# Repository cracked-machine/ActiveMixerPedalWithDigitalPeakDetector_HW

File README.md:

## Active 4-way mixer pedal with digital peak detector

- Analog 4->1 mixer circuit with buffered inputs and input gain control.
- Digital LED peak detector per input channel.
- Fits in a Hammond 1590BB enclosure (120mm x 95mm).

Required Kicad Hardware library: https://github.com/cracked-machine/KicadLibrary

Related SW project: https://github.com/cracked-machine/DigitalPeakDetector_SW

### System Overview

### Schematic

##### Top Level

##### Input Buffer and Gain Block

This uses a split supply op amp. The second stage is an inverting op amp configuration so that it can attenuate the input signal down to zero output.
Therefore the second op amp has very low input impedance and will cause "tone-suck" if used on its own. The solution is to add a preceding op amp stage in a non-inverting configuration that works as a high input impedance buffer.

##### Negative Rail Block

Each ``Input Buffer and Gain Block`` requires a split power supply. We use a charge pump to provide a negative voltage rail. The small SOT23-5 package provides ~10mA current, which is enough for a dual opamp in this design.

##### MCU Peak Detector block

This section replaces the classic analog peak detector circuit with a microcontroller. The input signal is captured by the 12bit ADC of the microcontroller. The average input value and the output threshold are determined by software. When the output threshold is reached, the microcontroller briefly toggles the LED. The on/off time duration of the LED is also determined in software.

##### MCU Input Buffer block

This serves several purposes.
1. It acts as a high impedance buffer and low pass filter for the ADC. This helps to provide a cleaner input signal for the ADC by removing high frequency noise.
2. The 3.3V *single* supply of the op amp removes any parts of the input signal that swing above 3.3v and below ground (the limits of the microcontroller). In the event that a line level input signal was plugged into the input, the op amp would be damaged before the microcontroller.

##### Power Supply block

This linear regulator drops the 9VDC input to 3.3VDC. The power requirements of the system components are very low (~65mA) so the expected dissipation is also low (0.37W). A copper pad on both sides of the PCB (with connected vias) is provided to reduce this dissipation.

## 3D Renderings

__PCB__

__Front Panel__

__Back Panel__

__PCB and panel profile__

## TODO

Some issues with the HW design:

- The PSU uses 3.3V for both MCU and Analog blocks. This is too low for the opamps in the analog blocks and does not allow enough headroom for the signal. This can result in clipping of the signal.

- The charge pumps used by the opamps in the analog blocks (used to create a negative voltage rail) need filtering. The negative voltage rail is noisy (observed on the scope) and a high pitched whine can be heard through the output when plugged into a large amplifier. A simple passive LPF would probably solve this. 

- The output is on the wrong side!

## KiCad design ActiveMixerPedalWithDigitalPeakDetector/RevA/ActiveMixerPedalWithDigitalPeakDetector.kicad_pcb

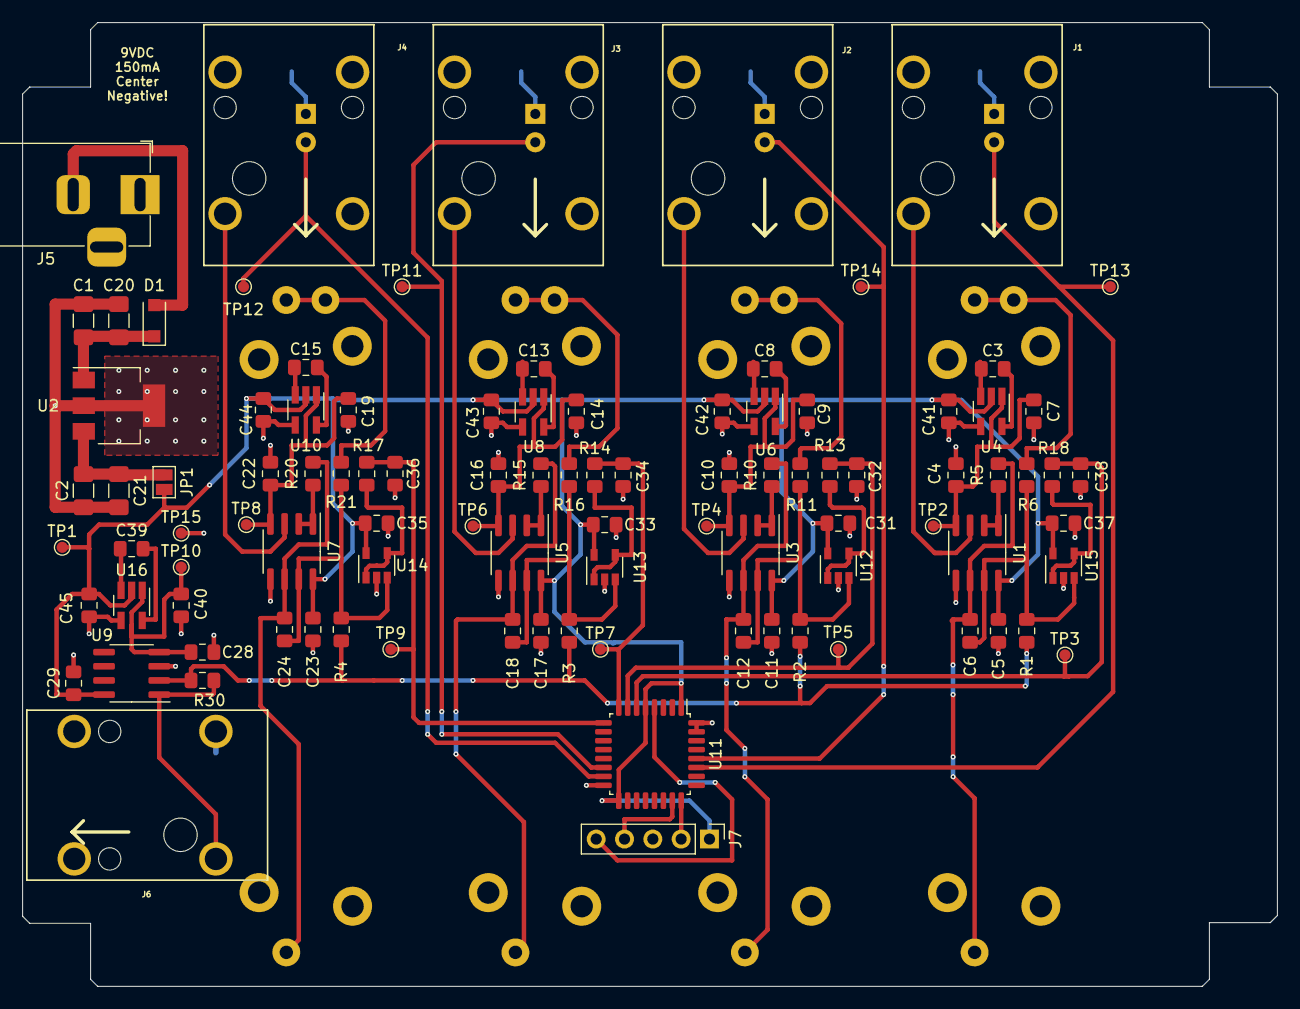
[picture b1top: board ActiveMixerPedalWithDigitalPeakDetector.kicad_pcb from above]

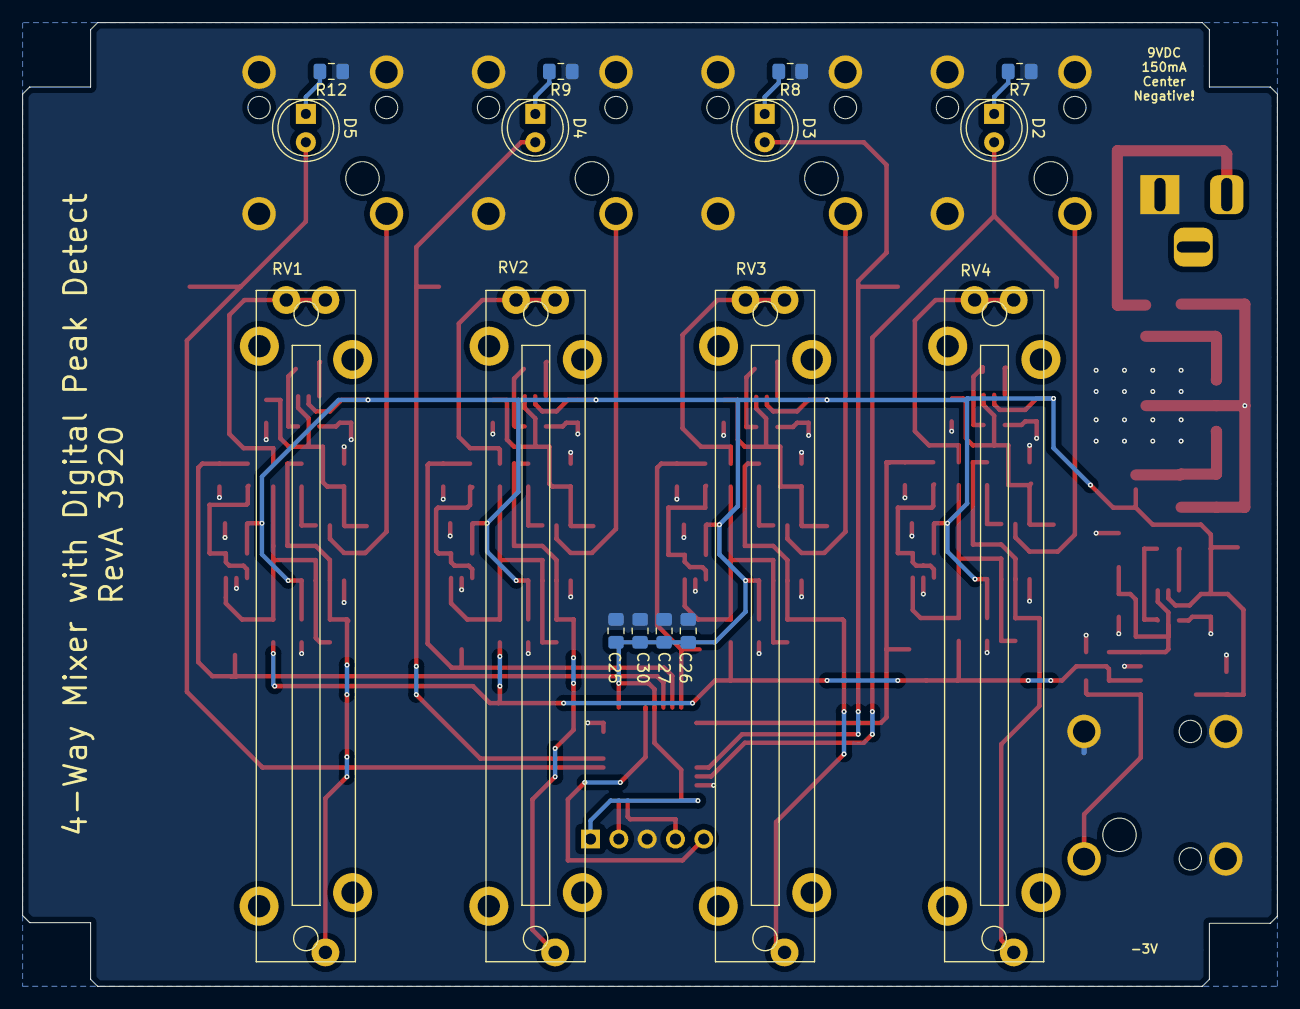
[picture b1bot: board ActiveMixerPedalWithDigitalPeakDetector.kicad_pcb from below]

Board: 2 copper layers, 112.5 x 86.4 mm, 114 parts (16 on the bottom side), 61 nets.

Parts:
C1, C21: 100nF; C_1206_3216Metric_Pad1.42x1.75mm_HandSolder
C2, C20: 1uF; C_1206_3216Metric_Pad1.42x1.75mm_HandSolder
C3, C7, C8, C9, C13, C14, C15, C19, C25, C39, C40, C41, C42, C43, C44, C45: 1uF; C_0805_2012Metric_Pad1.15x1.40mm_HandSolder
C4, C5, C10, C11, C16, C17, C22, C23, C26, C27, C28, C29, C30, C31, C32, C33, C34, C35, C36, C37, C38: 100nF; C_0805_2012Metric_Pad1.15x1.40mm_HandSolder
C6, C12, C18, C24: 1nF; C_0805_2012Metric_Pad1.15x1.40mm_HandSolder
D1: B0520LW-RH; D_SOD-123F
D2, D3, D4, D5: LED; LED_D5.0mm
J1, J2, J3, J4, J6: MonoJack2Switch; NRJxHx
J5: Barrel_Jack; BarrelJack_Horizontal
J7: Conn_01x05; PinHeader_1x05_P2.54mm_Vertical
JP1: Jumper_NO_Small; SolderJumper-2_P1.3mm_Open_Pad1.0x1.5mm
R1, R2, R3, R4, R30: 10K; R_0805_2012Metric_Pad1.15x1.40mm_HandSolder
R5, R10, R15, R20: 560R; R_0805_2012Metric_Pad1.15x1.40mm_HandSolder
R6, R11, R16, R21: 100R; R_0805_2012Metric_Pad1.15x1.40mm_HandSolder
R7, R8, R9, R12: R; R_0805_2012Metric_Pad1.15x1.40mm_HandSolder
R13, R14, R17, R18: 50R; R_0805_2012Metric_Pad1.15x1.40mm_HandSolder
RV1, RV2, RV3, RV4: 1K; Slider_PTA4543_60MM
TP1, TP2, TP3, TP4, TP5, TP6, TP7, TP8, TP9, TP10, TP11, TP12, TP13, TP14, TP15: TestPoint; TestPoint_Pad_D1.0mm
U1, U3, U5, U7, U9: TL072; SOIC-8_3.9x4.9mm_P1.27mm
U2: MCP1703A-3302_SOT223; SOT-223-3_TabPin2
U4, U6, U8, U10, U16: TPS60400; SOT-23-5_HandSoldering
U11: STM32F051K8Tx; LQFP-32_7x7mm_P0.8mm
U12, U13, U14, U15: MCP601-xOT; SOT-23-5

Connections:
+3V3: C5.1, C11.1, C17.1, C23.1, C25.1, C26.1, C27.1, C29.1, C30.1, C31.1, C33.1, C35.1, C37.1, C41.1, C42.1, C43.1, C44.1, C45.1, J7.1, JP1.2, TP1.1, U1.8, U3.8, U4.2, U5.8, U6.2, U7.8, U8.2, U9.8, U10.2, U11.1, U11.5, U11.17, U12.5, U13.5, U14.5, U15.5, U16.2
/InputBuffer1/NEG3VIN: C4.1, C7.1, TP2.1, U1.4, U4.1
/InputBuffer1/SIGNAL_INPUT: J1.1, U1.3
/InputBuffer2/NEG3VIN: C9.1, C10.1, TP4.1, U3.4, U6.1
/InputBuffer2/SIGNAL_INPUT: J2.1, U3.3
/InputBuffer3/NEG3VIN: C14.1, C16.1, TP6.1, U5.4, U8.1
/InputBuffer3/SIGNAL_INPUT: J3.1, U5.3
/InputBuffer4/NEG3VIN: C19.1, C22.1, TP8.1, U7.4, U10.1
/InputBuffer4/SIGNAL_INPUT: J4.1, U7.3
/OutputStage/NEG3VIN: C28.1, C40.1, TP10.1, U9.4, U16.1
/OutputStage/SIGNAL_INPUT: R1.1, R2.1, R3.1, R4.1, R30.1, U9.2
/OutputStage/SIGNAL_OUTPUT: J6.1, R30.2, U9.1
/PEAK_IN_BUF1: C6.1, R1.2, R6.1, U1.7, U15.3
/PEAK_IN_BUF2: C12.1, R2.2, R11.1, U3.7, U12.3
/PEAK_IN_BUF3: C18.1, R3.2, R16.1, U5.7, U13.3
/PEAK_IN_BUF4: C24.1, R4.2, R21.1, U7.7, U14.3
/PeakDetectorMCU/NRST: J7.5, U11.4
/PeakDetectorMCU/PEAK_IN_ADC1: C38.1, R18.1, TP3.1, U11.6
/PeakDetectorMCU/PEAK_IN_ADC2: C32.1, R13.1, TP5.1, U11.7
/PeakDetectorMCU/PEAK_IN_ADC3: C34.1, R14.1, TP7.1, U11.8
/PeakDetectorMCU/PEAK_IN_ADC4: C36.1, R17.1, TP9.1, U11.9
/PeakDetectorMCU/PEAK_OUT_PWM1: D5.2, TP13.1, U11.27
/PeakDetectorMCU/PEAK_OUT_PWM2: D4.2, TP14.1, U11.28
/PeakDetectorMCU/PEAK_OUT_PWM3: D3.2, TP11.1, U11.14
/PeakDetectorMCU/PEAK_OUT_PWM4: D2.2, TP12.1, U11.15
/PeakDetectorMCU/SYS_SWCLK: J7.2, U11.24
/PeakDetectorMCU/SYS_SWDIO: J7.4, U11.23
/PowerSupply/+9V_IN: D1.2, J5.2
GNDS: C1.2, C2.2, C4.2, C5.2, C7.2, C9.2, C10.2, C11.2, C14.2, C16.2, C17.2, C19.2, C20.2, C21.2, C22.2, C23.2, C25.2, C26.2, C27.2, C28.2, C29.2, C30.2, C31.2, C32.2, C33.2, C34.2, C35.2, C36.2, C37.2, C38.2, C40.2, C41.2, C42.2, C43.2, C44.2, C45.2, J1.2, J1.3, J1.4, J2.2, J2.3, J2.4, J3.2, J3.3, J3.4, J4.2, J4.3, J4.4, J5.1, J6.2, J6.3, J6.4, J7.3, R7.1, R8.1, R9.1, R12.1, TP15.1, U1.5, U2.2, U3.5, U4.4, U5.5, U6.4, U7.5, U8.4, U9.3, U10.4, U11.16, U11.31, U11.32, U12.2, U13.2, U14.2, U15.2, U16.4
unnamed: C1.1, C20.1, D1.1, U2.1
unnamed: C2.1, C21.1, JP1.1, U2.3
unnamed: C3.1, U4.3
unnamed: C3.2, U4.5
unnamed: C6.2, R5.1, RV1.3, U1.6
unnamed: C8.1, U6.3
unnamed: C8.2, U6.5
unnamed: C12.2, R10.1, RV2.3, U3.6
unnamed: C13.1, U8.3
unnamed: C13.2, U8.5
unnamed: C15.1, U10.3
unnamed: C15.2, U10.5
unnamed: C18.2, R15.1, RV3.3, U5.6
unnamed: C24.2, R20.1, RV4.3, U7.6
unnamed: C39.1, U16.3
unnamed: C39.2, U16.5
unnamed: D2.1, R7.2
unnamed: D3.1, R8.2
unnamed: D4.1, R9.2
unnamed: D5.1, R12.2
unnamed: R5.2, U1.1, U1.2
unnamed: R6.2, RV1.1, RV1.2
unnamed: R10.2, U3.1, U3.2
unnamed: R11.2, RV2.1, RV2.2
unnamed: R13.2, U12.1, U12.4
unnamed: R14.2, U13.1, U13.4
unnamed: R15.2, U5.1, U5.2
unnamed: R16.2, RV3.1, RV3.2
unnamed: R17.2, U14.1, U14.4
unnamed: R18.2, U15.1, U15.4
unnamed: R20.2, U7.1, U7.2
unnamed: R21.2, RV4.1, RV4.2

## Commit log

2020-09-23 hw update
    Completed RevA schematic
    TODO: complete RevA layout
2020-09-25 hw update
    RevA layout completed (draft)
2020-09-25 updated hw
    - added testpoints
2020-09-25 updated readme
    - Added overview block diagram
2020-09-25 updated readme
    updated system overview diagram
2020-09-26 updated system overview diagram
2020-09-26 updated readme
    added schema svg
2020-10-11 add layout dimension notes on dwg.user layer
2020-10-11 added front/back panel, updated readme
2020-10-12 updated front/back panel layout and gerbers
    - Changed mount holes to non-via
    - Changed BCu plane to FCu plane (same side as FCu silkscreen)
2020-10-13 added EnclosureInternalVerticalMeasurement.svg
2020-10-13 updated EnclosureInternalVerticalMeasurement.svg
2020-10-16 updated readme and added comments
2020-10-23 hardware update
    set led resistor value
2020-10-23 schematic update
    updated resistor (Rin) to 1K/10K
2020-10-24 updated frontpanel layout
    moved silk screen
